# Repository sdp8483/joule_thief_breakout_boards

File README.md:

# Joule Thief Breakout Boards for Breadboard Development
The following is a collection of breakout boards for test and development of the next version of the Multi LED Joule Thief.
* View the previous version here: [Multi LED Joule Thief V2015](https://samueldperry.com/2016/01/17/multi-led-joule-thief/ "Blog Article")
* View the next version here: IN DEVELOPMENT, NOT AVALIBLE

## KiCAD Files
The KiCAD files were created with KiCAD Version 4.0.7.
Custom libraries and footprints are included in this repository in the [lib_sch](https://github.com/sdp8483/joule_thief_breakout_boards/tree/master/lib_sch) 
and [lib_fp.pretty](https://github.com/sdp8483/joule_thief_breakout_boards/tree/master/lib_fp.pretty) files. Footprints have been adjusted for at home etching 
using the photo resist method by increasing the annular ring around the pin headers. There is no reason these boards could not be sent to a prototype PCB fabricator 
such as OSHpark but for fast quick prototyping at home etching should be good enough.

For details about etching at home see the following excellent articles:
* http://www.electricstuff.co.uk/pcbs.html
* http://quinndunki.com/blondihacks/?p=835

## Image Files
KiCAD was then used to output a SVG file of the PCB layout with only the back copper layer visible, un-mirrored. The SVG file was imported into GIMP at a high dpi 
where each board was then split up into a separate .xcf file. The image was then inverted and doubled in for preparation for printing on laser printer transparencies.
The xcf files can be directly printed from or image files can be exported from them for printing. Make sure to have the maximum dpi that the printer can handle 
for sharp lines.

## Etching
A dry film pcb resist was used for etching. The item was purchased from [Amazon](https://www.amazon.com/INSMA-Photosensitive-Circuit-Production-Photoresist/dp/B01C5SUMAC/ref=sr_1_1?ie=UTF8&qid=1507471425&sr=8-1&keywords=pcb+photoresist) and the manufacture offers some [instructions](https://www.youtube.com/watch?v=cRCFGZxmob0) on use.
Following the manufactures instructions along with the instructions from the articles linked above gave good results.

## Components
The following components were identified for investigation for not only the next version Joule Thief but also for measurement:
* [SRF4532-510Y](https://www.digikey.com/product-detail/en/bourns-inc/SRF4532-510Y/SRF4532-510YCT-ND/3679940): This component was used in the [Joule Thief Candle](https://samueldperry.com/2016/12/18/single-led-candle-joule-thief/)
* [SRF2012-900YA](https://www.digikey.com/product-detail/en/bourns-inc/SRF2012-900YA/SRF2012-900YACT-ND/2681270): Test to see if this lower cost inductor could replace the SRF4532-510Y, hint it does not work :P
* [MP-2016-1100-65-70](https://www.digikey.com/product-detail/en/luminus-devices-inc/MP-2016-1100-65-70/1214-1298-1-ND/5287132): Bright cool white smd led to replace 3mm leds
* [INA180A2IDBVT](https://www.digikey.com/product-detail/en/texas-instruments/INA180A2IDBVT/296-46628-1-ND/7219064): Current measurements during development
* [INA180A4IDBVT](https://www.digikey.com/product-detail/en/texas-instruments/INA180A4IDBVT/296-46630-1-ND/7219066): Higher gain current measurements
* [RUT2012FR100CS](https://www.digikey.com/product-detail/en/samsung-electro-mechanics-america-inc/RUT2012FR100CS/1276-6170-1-ND/3969142): Current shunt

## Testing and Development
Test results are available in the testing directory of this repository as an spreadsheet.

Assemble the joule thief circuit on a pcb with jumper wires. A resistor for the base of the NPN transistor is the only other component required for the joule thief circuit. Adjust this resistance 
value to change the current draw of the device.

The joule thief circuit is powered by an adjustable lab power supply for testing, a DPS5015 was used. Input current was measured using a Owon B41T+ in the mA range.
Input voltage was measured after the current meter to remove burden voltage. This was measured using a Owon B41T+.

The INA180A4IDBVT breakout board with a 0.1ohm 1% shut was used to monitor the LED current. The current sensor was powered by an external 3.3V
power supply. An AN8008 DMM was used to measure the output of this current sensor.

A TEMT6000 light sensor was placed approximately 25mm from the LED. To prevent external ambient light from impacting light measurements a paper tube was constructed with a black inside diameter and placed between the LED and light sensor.
The output from the light sensor was measured using a BK Precision 2709B.

Switching frequency was measured at the anode of the LED with respect to ground. An AN8008 DMM was used to measure the frequency.

An oscilloscope was used to observe signals but measurements were not recorded.

## More
That is all. If you have stumbled upon the repository and can offer any suggestions contact me through github. I used the previous Multi LED Joule Thief as a 
learning experience in PCB design, fabrication, and assembly. I'm still learning so help is appreciated.

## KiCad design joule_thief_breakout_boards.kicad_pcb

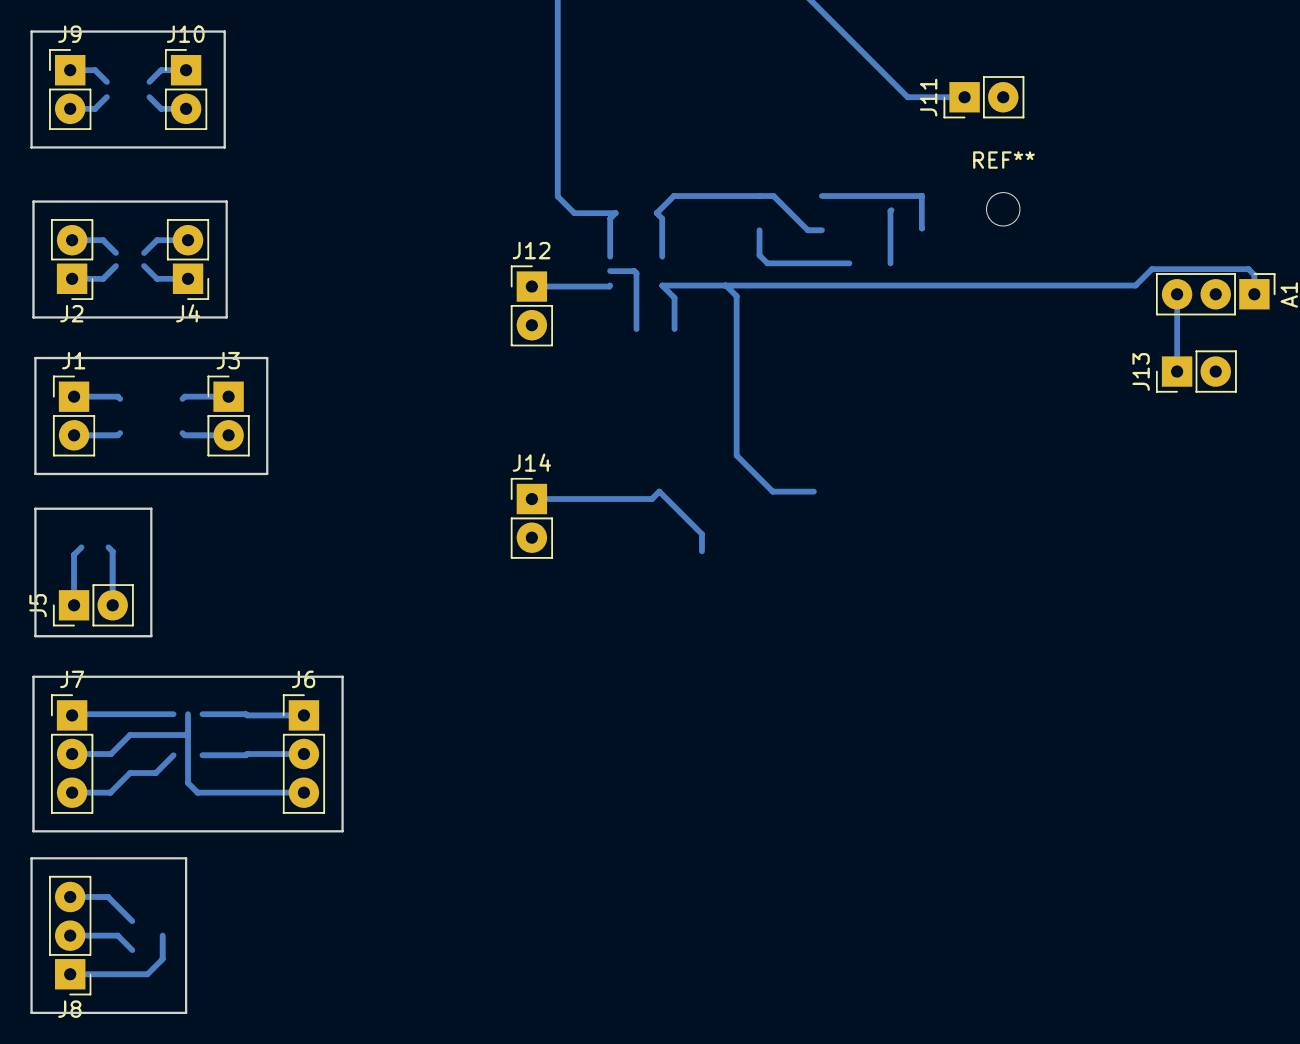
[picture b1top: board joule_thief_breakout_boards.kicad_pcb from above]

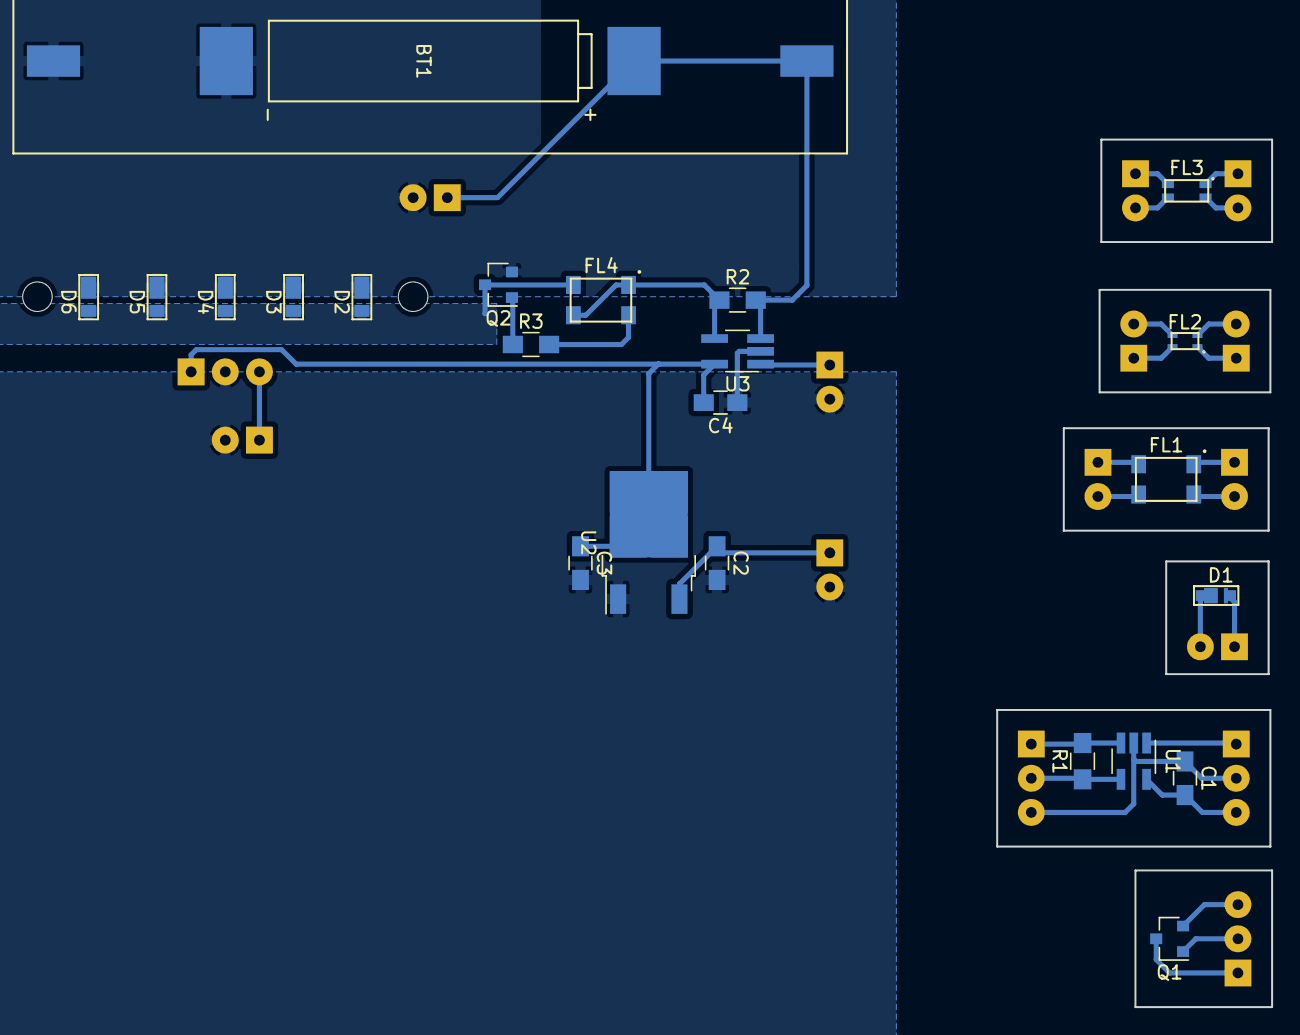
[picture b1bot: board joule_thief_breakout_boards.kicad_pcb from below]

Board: 2 copper layers, 38 parts (23 on the bottom side), 33 nets.

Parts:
A1: TEMT600; Etch_Pin_Header_Straight_1x03_Pitch2.54mm
BT1: AA Cell; BK-53_MPD_AAClip
C1, C4: 0.1uF; C_0805_HandSoldering
C2, C3: 10uF; C_0805_HandSoldering
D1, D2, D3, D4, D5, D6: LED; LED_Luminus_MP-2016
FL1: SRF4532-510Y; SRF4532_Bourns_CMI
FL2: SRF2012-900YA; SRF2012_Bourns_CMI
FL3: SRF3216-222Y; SRF3216_Bourns_CMI
FL4: Bourns_Common_Mode_Inductor; SRF4532_Bourns_CMI
J1, J2, J3, J4, J5, J9, J10: Conn_01x02; Etch_Pin_Header_Straight_1x02_Pitch2.54mm
J6, J7, J8: Conn_01x03; Etch_Pin_Header_Straight_1x03_Pitch2.54mm
J11: Voltage; Etch_Pin_Header_Straight_1x02_Pitch2.54mm
J12: Current; Etch_Pin_Header_Straight_1x02_Pitch2.54mm
J13: Light; Etch_Pin_Header_Straight_1x02_Pitch2.54mm
J14: PWR; Etch_Pin_Header_Straight_1x02_Pitch2.54mm
Q1, Q2: BC817-40; SOT-23
R1, R2: 0.1; R_0805_HandSoldering
R3: R; R_0805_HandSoldering
U1: INA180; SOT-23-5_HandSoldering
U2: NCP1117-3.3; TO-252-2
U3: INA180A4; TSOT-23-5_HandSoldering

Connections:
+3V3: A1.1, C3.1, C4.2, U2.2, U3.5
+5V: C2.1, J14.1, U2.3
GND: BT1.2, D2.1, D3.1, D4.1, D5.1, D6.1, J11.2, Q2.2
GNDA: A1.2, C2.2, C3.2, C4.1, J12.2, J13.2, J14.2, U2.1, U3.2
unnamed: A1.3, J13.1
unnamed: BT1.1, J11.1, R2.2, U3.3
unnamed: C1.1, J6.3, J7.2, U1.2
unnamed: C1.2, J7.3, U1.5
unnamed: D1.1, J5.1
unnamed: D1.2, J5.2
unnamed: D2.2, D3.2, D4.2, D5.2, D6.2, FL4.2, Q2.3
unnamed: FL1.1, J1.1
unnamed: FL1.2, J3.1
unnamed: FL1.3, J3.2
unnamed: FL1.4, J1.2
unnamed: FL2.1, J2.1
unnamed: FL2.2, J4.1
unnamed: FL2.3, J4.2
unnamed: FL2.4, J2.2
unnamed: FL3.1, J9.1
unnamed: FL3.2, J10.1
unnamed: FL3.3, J10.2
unnamed: FL3.4, J9.2
unnamed: FL4.1, FL4.3, R2.1, U3.4
unnamed: FL4.4, R3.2
unnamed: J6.1, R1.2, U1.3
unnamed: J6.2, R1.1, U1.4
unnamed: J7.1, U1.1
unnamed: J8.1, Q1.3
unnamed: J8.2, Q1.1
unnamed: J8.3, Q1.2
unnamed: J12.1, U3.1
unnamed: Q2.1, R3.1

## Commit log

2017-10-04 boards layout
2017-10-04 header pin swaping for easy lineup with pcb
2017-10-04 header pin footprints with extra copper for etching
2017-10-04 removed pad offsets
2017-10-04 created pcb layout
2017-10-06 add transistor breakout
2017-10-06 added npn transistor symbol and conn_01x03
2017-10-06 transistor breakout pcb layout
2017-10-07 no dummy needed
2017-10-07 save pcb to svg
2017-10-07 changed header for transistor footprint to custom etch footprint
2017-10-07 update CvPCB to reflect header footprint change in Pcbnew
2017-10-07 update svg with new footprint
2017-10-07 initial gimp file creation for srf4532 breakout
2017-10-07 wrong part number, file renamed
2017-10-07 initial gimp file creation for led breakout
2017-10-07 initial gimp file creation for current sensor breakout
2017-10-07 initial gimp file creation for npn transistor breakout
2017-10-07 saved as no mirror
2017-10-07 un mirrored image
2017-10-07 file creation of all breakout negatives for printing
2017-10-07 size not correct, print each file instead
2017-10-07 double negative, ready to print
2017-10-08 unhide PCB layers
2017-10-08 update with more information
2017-10-14 ignore temp excel files
2017-10-14 initial commit testing results
2017-10-14 add info to testing and development
2017-10-14 plots on seperate tabs
2017-10-14 add SRF3216 footprint
2017-10-14 add SRF3216 breakout
2017-10-14 annotate new componets, update net list
2017-10-14 add SRF3216 breakout PCB layout
2017-10-15 add TEMT6000
2017-10-15 add complete joule thief with measurements sensors
2017-10-15 aa battery clip footprint, assosiate symbols with footprints for sensor joule thief
2017-10-15 change schematic sheet name
2017-10-15 add schematic notes for sensors
2017-10-15 Specify gain of INA180 as A4 (200) for joule thief with sensors
2017-10-15 add header for sensor 5V power
2017-10-15 update pin header footprints for new board to use etch footprint
2017-10-15 simplify LED footprint
2017-10-15 add joule thief with measurement points
2017-10-15 add keepout area around positive battery clip, no touchy ground plane!
2017-10-15 update testing and development section
2017-10-20 add full jt pcb layout
2017-10-20 negative ready for pcb etch
2017-10-20 add full jt pcb
2017-10-20 init commit
2017-10-21 set value of R3
2017-10-23 removed accuracy of DMMs
2017-12-03 wow, spelling
2017-12-03 new charts
